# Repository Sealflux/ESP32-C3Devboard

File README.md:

# ESP32-C3Devboard
## Description
Custom ESP32-C3 Devboard with bulit in charging, wifi and antenna.
## Features
- ESP32-C3 which has wifi capabilities along with bulit in charging for lipo battery.
- 16 MB of onboard flash storage
- Charges through USB-C
- Tactile button to reset.
## Hardware
- ESP32-C3
- BLE Wifi
- Battery Charging
- Lots and lots of capacitors and resistors

# Bill Of Materials (BOM)
| Designator | Part | Qty | Cost (each) | Total | Link | LCSC # |
|------------|------|:---:|------------|-------|------|--------|
| BT1 | Battery Cell | 1 | Depends on battery | Depends on battery | Depends on battery | N/A |
| C1, C5, C6, C7 | 100nF Capacitor (0402) | 4 |$0.0073|$0.73| [LCSC](https://lcsc.com/product-detail/C60474.html) | C60474 |
| C2, C3, C4, C9 | 10µF Capacitor (0603) | 4 |$0.0411|$0.82| [LCSC](https://lcsc.com/product-detail/C85713.html) | C85713 |
| C8 | 1µF Capacitor (0603) | 1 |$0.0225|$1.13| [LCSC](https://lcsc.com/product-detail/C29936.html) | C29936 |
| J1 | USB-C Receptacle USB2.0 14P | 1 |$0.1709|$0.1709| [LCSC](https://www.lcsc.com/product-detail/C165948.html) | C165948 |
| J2, J3 | 1x12 Pin Header (2.54mm) | 2 |N/A|Generic, use whatever you want.| N/A | N/A |
| R1, R11 | 1kΩ Resistor (0603) | 2 |$0.0045|0.45 | [LCSC](https://lcsc.com/product-detail/C2907002.html) | C2907002 |
| R2, R8, R9, R10 | 10kΩ Resistor (0402) | 4 |$0.0038|0.38| [LCSC](https://lcsc.com/product-detail/C60490.html) | C60490 |
| R3, R4 | 5.1kΩ Resistor (0603) | 2 |$0.0027|0.27| [LCSC](https://lcsc.com/product-detail/C2907044.html) | C2907044 |
| R6 | 2.2kΩ Resistor (0402) | 1 |$0.0024|$0.24| [LCSC](https://lcsc.com/product-detail/C2906865.html) | C2906865 |
| SW1, SW2 | Push Button Switch (B3U-1000PM) | 2 |$0.1869|$0.93|[LCSC](https://www.lcsc.com/product-detail/C231329.html)| C231329 |
| U1 | ESP32-C3 (QFN-32) | 1 |N/A|Depends on where you buy from|[Datasheet](https://www.espressif.com/sites/default/files/documentation/esp32-c3_datasheet_en.pdf) | N/A |
| U2 | W25Q16JVUXIQ (USON-8) | 1 |$1.6193|$1.6193| [LCSC](https://lcsc.com/product-detail/C2843335.html) | C2843335 |
| U3 | H7233-1 LDO (SOT-23-3) | 1 |$0.1102|$0.55| [LCSC](https://lcsc.com/product-detail/C277859.html) | C277859 |
| U4 | TP4056 Battery Charger (ESOP-8) | 1 |$0.1864|$0.93 | [LCSC](https://lcsc.com/product-detail/C16581.html) | C16581 |
| | **Shipping** | | | Depends on your address | | |
| | **Total Costs** | | | Without shipping | | |

## Steps To Reproduce
1. Download the gerbers.zip from production folder
2. Manufacture the PCBs from whatever manufacturer you want using the gerbers.zip
3. Order the components from BOM
4. Solder the components onto the PCBs
5. Enjoy your dev board!
## Schematic

## PCB

## PCBA

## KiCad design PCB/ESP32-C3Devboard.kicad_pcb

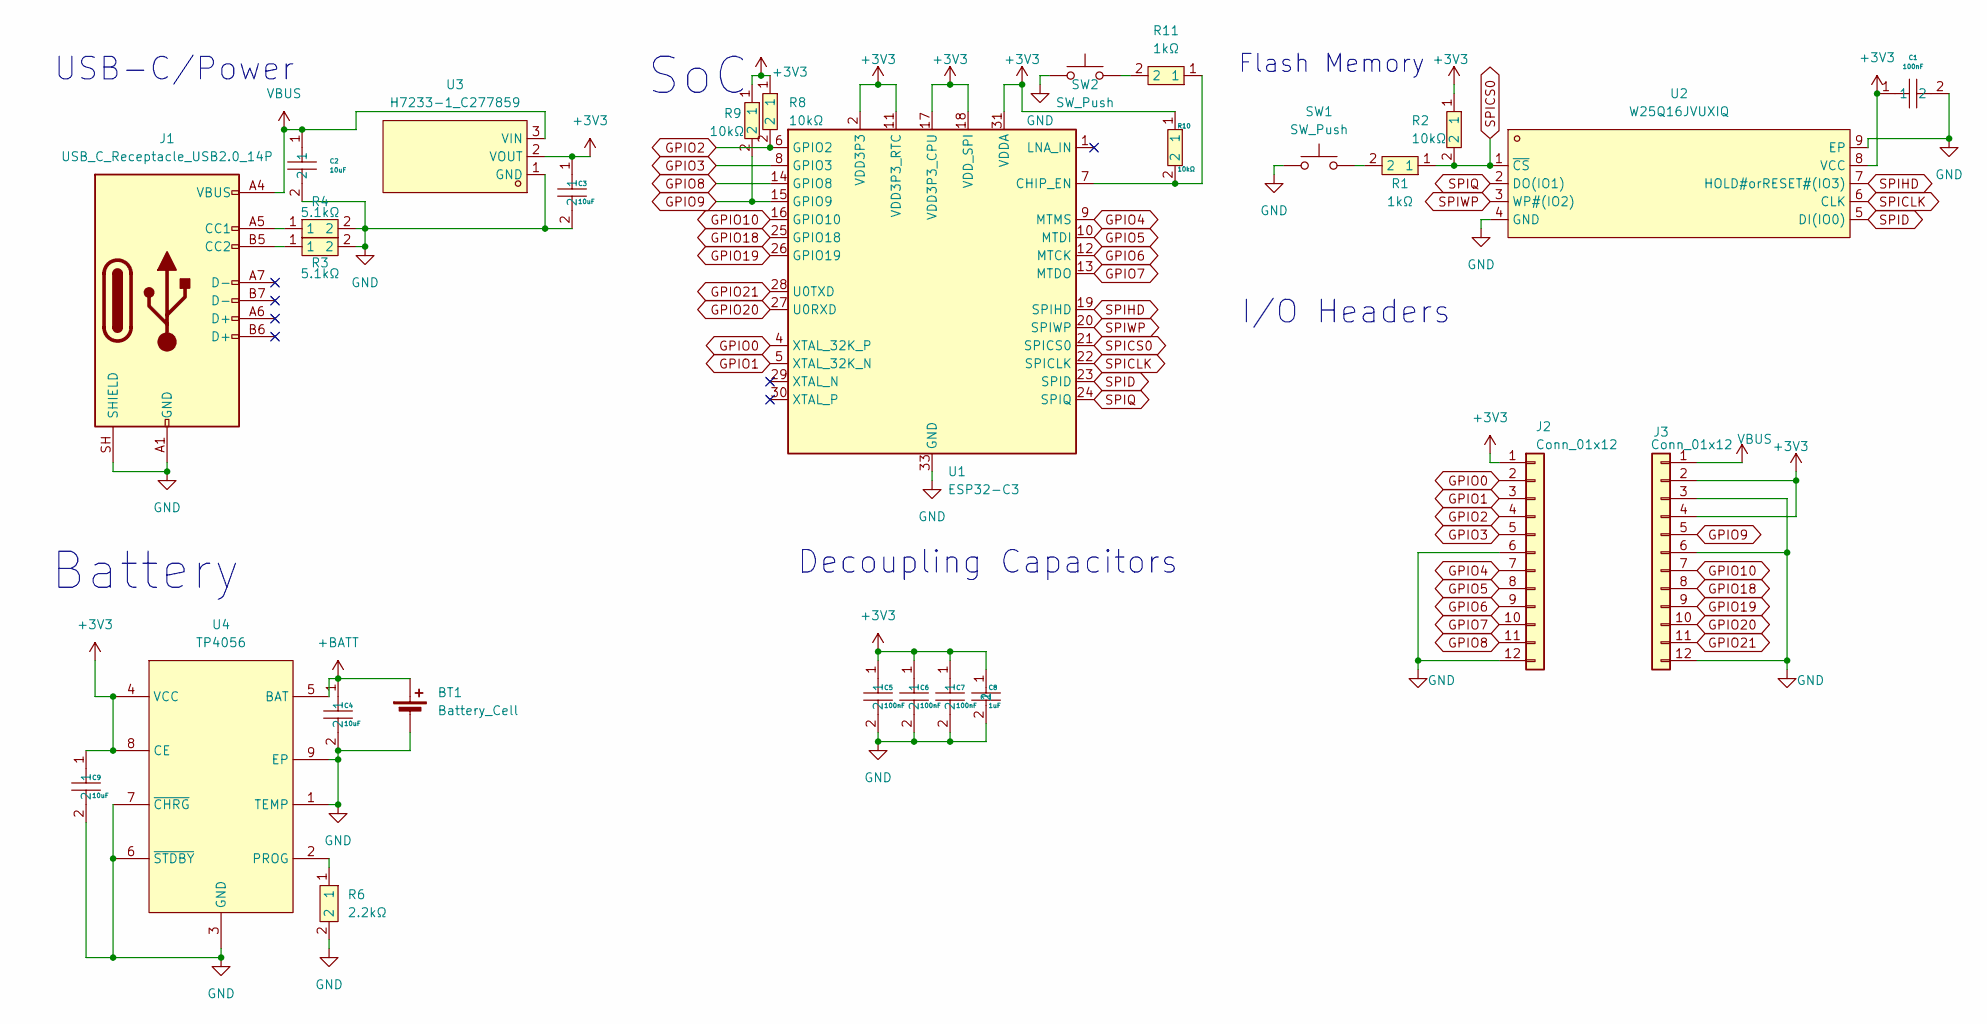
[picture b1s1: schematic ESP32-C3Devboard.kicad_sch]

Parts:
BT1: Battery_Cell; PinHeader_1x02_P2.54mm_Vertical
C1, C5, C6, C7: 100nF; C0402; MPN CC0402KRX7R7BB104; LCSC Part C60474
C2, C3, C4, C9: 10uF; C0603; MPN CL10A106MP8NNNC; LCSC Part C85713
C8: 1uF; C0603; MPN CL10B105KA8NNNC; LCSC Part C29936
J1: USB_C_Receptacle_USB2.0_14P; USB_C_Receptacle_HRO_TYPE-C-31-M-12
J2, J3: Conn_01x12; PinHeader_1x12_P2.54mm_Vertical
R1, R11: 1kΩ; R0603; MPN FRC0603F1001TS; LCSC Part C2907002
R2, R8, R9, R10: 10kΩ; R0402; MPN RC0402FR-0710KL; LCSC Part C60490
R3, R4: 5.1kΩ; R0603; MPN FRC0603F5101TS; LCSC Part C2907044
R6: 2.2kΩ; R0402; MPN FRC0402F2201TS; LCSC Part C2906865
SW1, SW2: SW_Push; KEY-SMD_B3U-1000PM
U1: ESP32-C3; QFN-32-1EP_5x5mm_P0.5mm_EP3.7x3.7mm
U2: W25Q16JVUXIQ; USON-8_L3.0-W2.0-P0.50-BL-EP; MPN W25Q16JVUXIQ; LCSC Part C2843335
U3: H7233-1_C277859; SOT-23-3_L2.9-W1.3-P1.90-LS2.4-BR; MPN H7233-1; LCSC Part C277859
U4: TP4056; ESOP-8_L4.9-W3.9-P1.27-LS6.0-BL-EP; MPN TP4056-42-ESOP8; LCSC Part C16581

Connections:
+3V3: C1.1, C3.1, C5.1, C6.1, C7.1, C8.1, C9.1, J2.1, J3.2, J3.4, R2.1, R8.1, R9.1, R10.1, U1.2 (VDD3P3), U1.3 (VDD3P3), U1.11 (VDD3P3_RTC), U1.17 (VDD3P3_CPU), U1.18 (VDD_SPI), U1.31 (VDDA), U1.32 (VDDA), U2.8 (VCC), U3.2 (VOUT), U4.4 (VCC), U4.8 (CE); also elsewhere on the board
+BATT: BT1.1 (+), C4.1, U4.5 (BAT)
GND: BT1.2 (-), C1.2, C2.2, C3.2, C4.2, C5.2, C6.2, C7.2, C8.2, C9.2, J1.A1 (GND), J1.A12 (GND), J1.B1 (GND), J1.B12 (GND), J1.SH (SHIELD), J2.6, J2.12, J3.3, J3.6, J3.12, R3.2, R4.2, R6.2, SW1.1, SW2.1, U1.33 (GND), U2.4 (GND), U2.9 (EP), U3.1 (GND), U4.1 (TEMP), U4.3 (GND), U4.6 (~STDBY), U4.7 (~CHRG), U4.9 (EP); also elsewhere on the board
GPIO0: J2.2, U1.4 (XTAL_32K_P)
GPIO1: J2.3, U1.5 (XTAL_32K_N)
GPIO2: J2.4, R8.2, U1.6 (GPIO2)
GPIO3: J2.5, U1.8 (GPIO3)
GPIO4: J2.7, U1.9 (MTMS)
GPIO5: J2.8, U1.10 (MTDI)
GPIO6: J2.9, U1.12 (MTCK)
GPIO7: J2.10, U1.13 (MTDO)
GPIO8: J2.11, U1.14 (GPIO8)
GPIO9: J3.5, R9.2, U1.15 (GPIO9)
GPIO10: J3.7, U1.16 (GPIO10)
GPIO18: J3.8, U1.25 (GPIO18)
GPIO19: J3.9, U1.26 (GPIO19)
GPIO20: J3.10, U1.27 (U0RXD)
GPIO21: J3.11, U1.28 (U0TXD)
unnamed: J1.A5 (CC1), R4.1
unnamed: J1.B5 (CC2), R3.1
unnamed: R1.2, SW1.2
unnamed: R11.2, SW2.2
unnamed: R10.2, R11.1, U1.7 (CHIP_EN)
unnamed: R6.1, U4.2 (PROG)
SPICLK: U1.22 (SPICLK), U2.6 (CLK)
SPICS0: R1.1, R2.2, U1.21 (SPICS0), U2.1 (~CS)
SPID: U1.23 (SPID), U2.5 (DI(IO0))
SPIHD: U1.19 (SPIHD), U2.7 (HOLD#orRESET#(IO3))
SPIQ: U1.24 (SPIQ), U2.2 (DO(IO1))
SPIWP: U1.20 (SPIWP), U2.3 (WP#(IO2))
VBUS: C2.1, J1.A4 (VBUS), J1.A9 (VBUS), J1.B4 (VBUS), J1.B9 (VBUS), J3.1, U3.3 (VIN)

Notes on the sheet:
Decoupling Capacitors
Flash Memory
I/O Headers
SoC
Battery
USB-C/Power

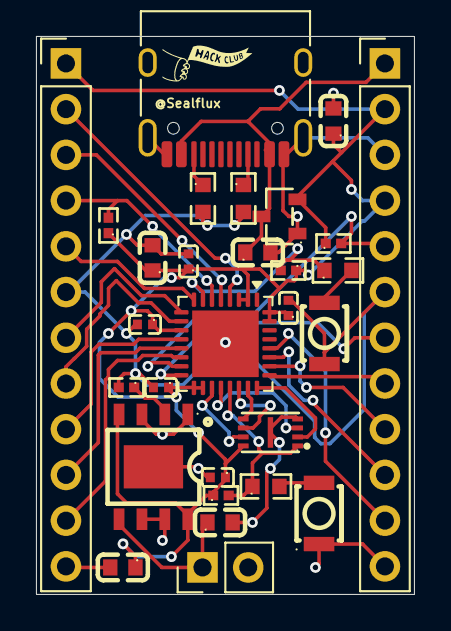
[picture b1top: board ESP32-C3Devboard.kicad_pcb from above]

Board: 2 copper layers, 21.0 x 31.0 mm, 29 parts (0 on the bottom side), 31 nets.

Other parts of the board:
C8#2: 1uF; C0603

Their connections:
+3V3: C8#2.1; also elsewhere on the board
GND: C8#2.2; also elsewhere on the board
